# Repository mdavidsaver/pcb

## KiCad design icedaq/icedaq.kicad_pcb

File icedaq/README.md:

iceDAQ
======

Spec.

* 2x DAC
* 2x ADC
* 4x DIO
* SPI interface to controller
* Raspberry Pi Hat
* iCE40 FPGA

Connections to iCE40 FPGA
-------------------------

Programming interface for iCE40 is attached to SPI1 of CPU.  Low speed SPI1 used to configure FPGA, and for debugging of primary interface.  Uses SPI1_CE2 pin to simplify layout.

iCE40 reset and configuration done connected to GPIO pins.

Application program uses SPI0 of CPU to arbitrary I/O pins of iCE40.  Use SPI0_CE0.

i2c eeprom for rpi hat discovery.

Route global clocks 0 and 1 from CPU to iCE40 global inputs

External crystal oscillator connected to iCE40 global input.

Break out UART0 for no particular reason.

Additional SPI connections to 2x ADC and 2x DAC chips.

Break out 4x GPIO pins to header

Analog output
-------------

Use 2x TI DACx311 series SPI DAC.

Operate w/ 3.3V supply.  Could use 5V supply directly as SPI is MOSI only.

output into opamp in non-inverting topology.  Gain=1.5 gives output range of 0-5V from 0-3.3V input.

opamp output has space for series and ground termination.

Analog input
------------

Use 3x TI ADC082S021 (50 KS/S -> 200 KS/S) two channel ADC.  Only one channel per chip used.

Operate w/ 3.3V supply.

input from opamp in non-inverting topology through 0.66 resistor divider (5V -> 3.3V).
opamp gain=1.

input of opamp has space for series and ground termination, also option of AC coupling w/ resistor bias network.

Op Amp
------

Microchip MCP6001 quad rail-to-rail opamp.

Operate w/ 5V supply.

Power budget
------------

Maximum current consumption

3.3V

* iCE40

  <8mA per I/O driver

* eeprom Microchip 24LC23

  <3mA

* 2x DACx311

  short circuit output current @3V = 20mA, @5V = 50mA.

* 2x ADC

  <20mA

* oscillator
* 1.2V regulator

5V

* opamp MCP6001

  <=30 mA
  short circuit output current @1.8V = 6mA, @5.5V = 23 mA

1.2V

* iCE40

  <1mA continuous
  <20mA peak startup

Safety
------

MCP6001 outputs may be shorted w/o damage.  input voltage must be within 1V of supply range.

References
----------

Raspberry Pi

https://github.com/raspberrypi/hats/blob/master/designguide.md

https://pinout.xyz/

https://www.raspberrypi.org/documentation/hardware/raspberrypi/schematics/RPI-3B-V1_2-SCHEMATIC-REDUCED.pdf

iCE40

http://www.latticesemi.com/~/media/LatticeSemi/Documents/Handbooks/iCE40FamilyHandbook.pdf

ADC

http://www.ti.com/lit/ds/symlink/adc082s021.pdf

DAC

http://www.ti.com/lit/ds/symlink/dac5311.pdf

opamp

http://ww1.microchip.com/downloads/en/DeviceDoc/21733j.pdf

eeprom

http://ww1.microchip.com/downloads/en/DeviceDoc/21072G.pdf

iCE40 pins
----------

set_io	GPIO2[0]	1
set_io	GPIO2[1]	2
set_io	GPIO2[2]	3
set_io	GPIO2[3]	4
set_io	GPIO3[0]	18
set_io	GPIO3[1]	19
set_io	GPIO3[2]	20
set_io	GPIO3[3]	21
set_io	GPIO0[3]	27
set_io	GPIO0[2]	28
set_io	GPIO0[1]	29
set_io	GPIO0[0]	30
set_io	GCLK0	33
set_io	GCLK1	34
set_io	SPI1_MISO	45
set_io	SPI1_MOSI	46
set_io	SPI1_SCK	48
set_io	SPI1_CE2	49
set_io	SPI0_CE0	51
set_io	SPI0_SCLK	52
set_io	SPI0_MISO	53
set_io	SPI0_MOSI	54
set_io	ADC0_CE	56
set_io	ADC0_SCK	57
set_io	ADC0_MISO	59
set_io	ADC0_MOSI	60
set_io	ADC1_CE	64
set_io	ADC1_SCK	65
set_io	ADC1_MISO	66
set_io	ADC1_MOSI	68
set_io	DAC0_MOSI	78
set_io	DAC0_SCK	79
set_io	DAC0_SYNC	80
set_io	DAC1_MOSI	82
set_io	DAC1_SCK	83
set_io	DAC1_SYNC	85
set_io	CLK	90

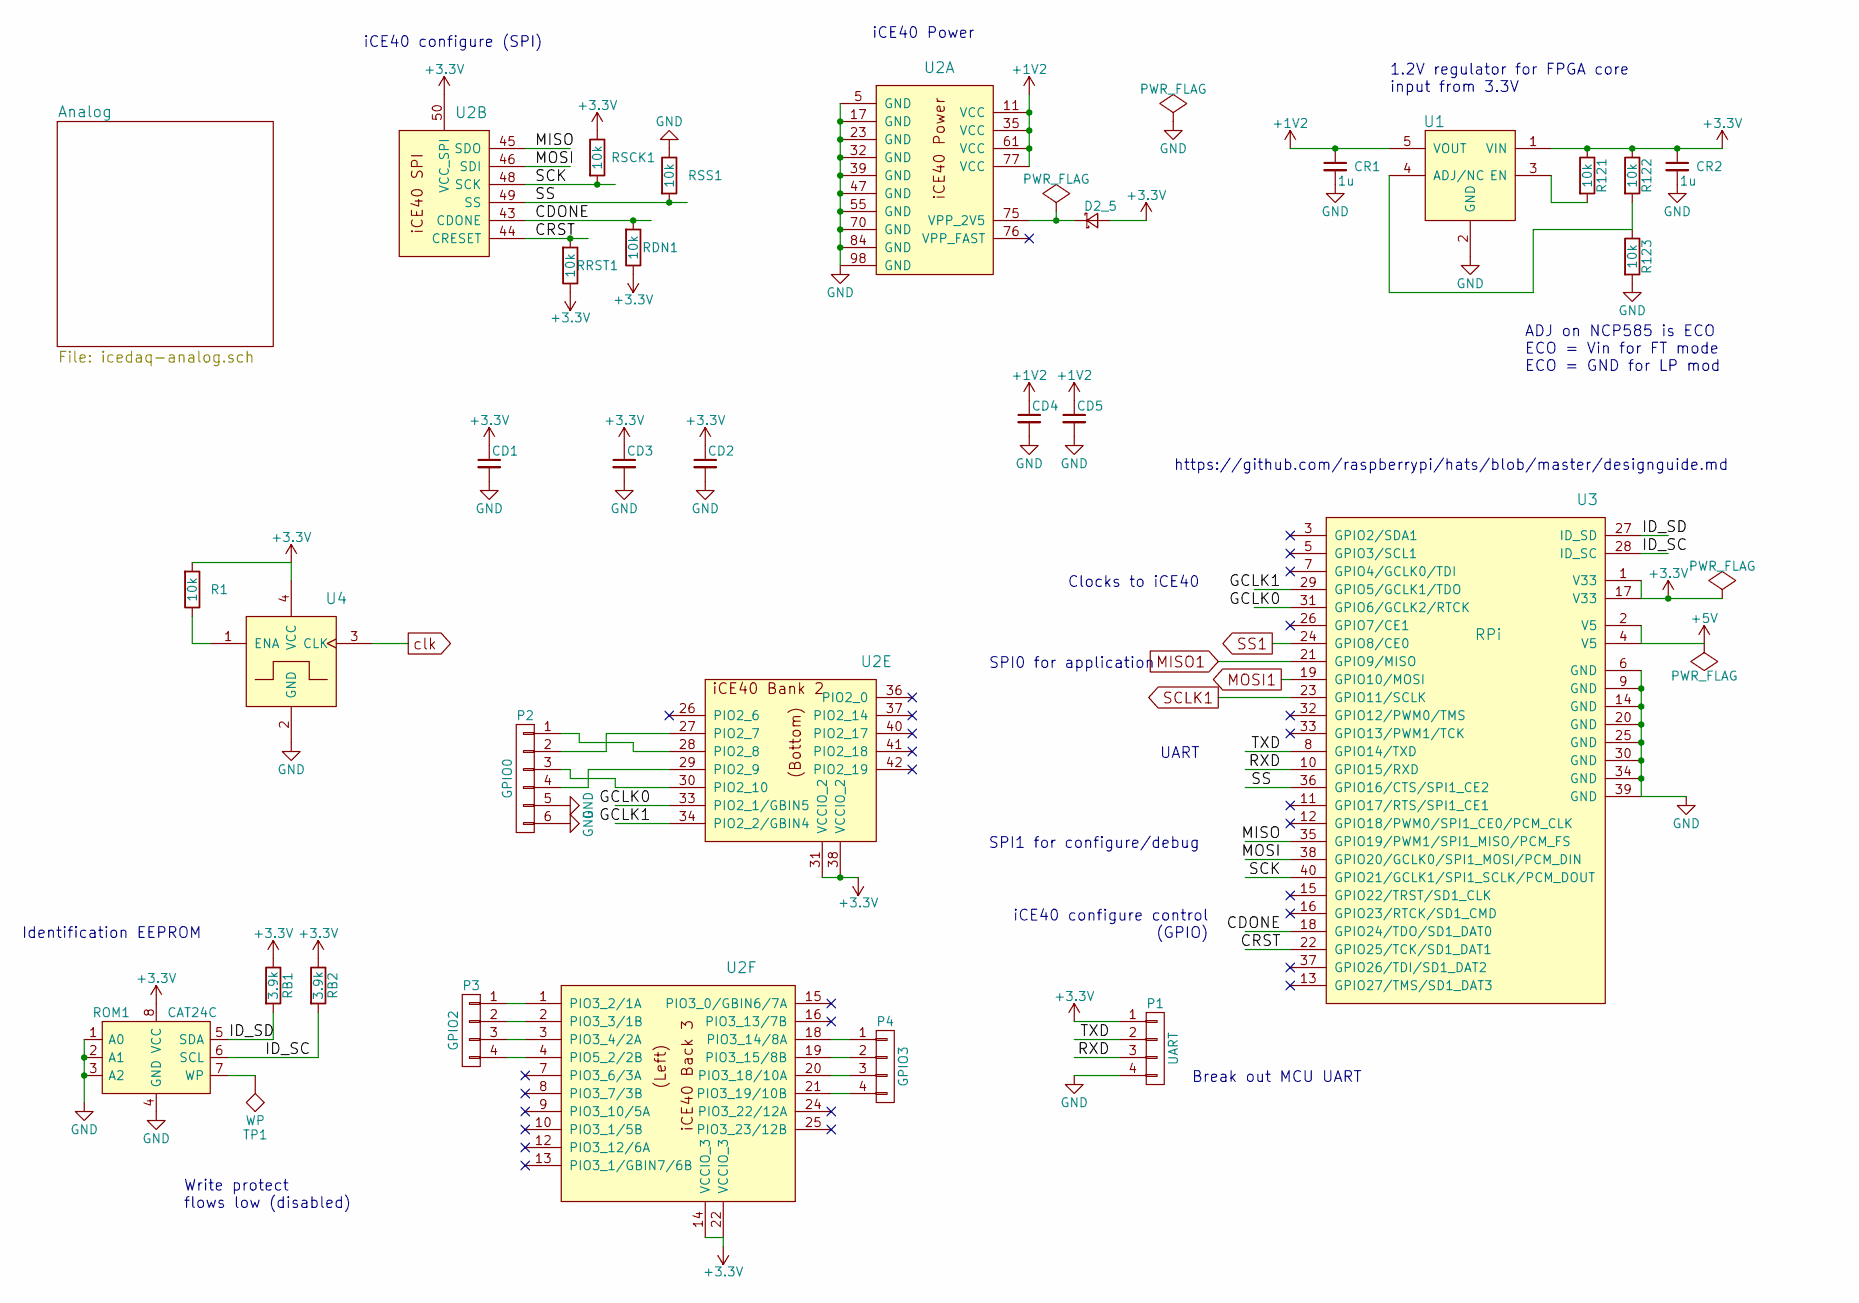
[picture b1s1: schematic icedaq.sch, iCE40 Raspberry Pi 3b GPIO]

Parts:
CD1, CD2, CD3, CD4, CD5: C_Small; C_0603_HandSoldering
CR1, CR2: 1u; C_0603_HandSoldering
D2_5: D_Schottky_Small; D_0603_HandSoldering
P1: UART; Pin_Header_Straight_1x04
P2: GPIO0; Pin_Header_Straight_2x03
P3: GPIO2; gpio
P4: GPIO3; gpio
R1, R121, R122, R123: 10k; R_0603_HandSoldering
RB1, RB2: 3.9k; R_0603_HandSoldering
RDN1: 10k; R_0603_HandSoldering
ROM1: CAT24C; SOIC-8_3.9x4.9mm_Pitch1.27mm
RRST1: 10k; R_0603_HandSoldering
RSCK1: 10k; R_0603_HandSoldering
RSS1: 10k; R_0603_HandSoldering
TP1: WP; testpoint
U1: REG12; SOT23-5
U2: iCE40HX1K-VQ100; VQFP-100
U3: RPi; Pin_Header_Straight_2x20
U4: oscillator4; OSC_SMD_1

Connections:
+1V2: CD4.1, CD5.1, CR1.1, U1.5 (VOUT), U2.11 (VCC), U2.35 (VCC), U2.61 (VCC), U2.77 (VCC)
+3V3: CD1.1, CD2.1, CD3.1, CR2.1, D2_5.2 (A), P1.1, R1.2, R121.1, R122.1, RB1.1, RB2.1, RDN1.1, ROM1.8 (VCC), RRST1.1, RSCK1.1, U1.1 (VIN), U2.14 (VCCIO_3), U2.22 (VCCIO_3), U2.31 (VCCIO_2), U2.38 (VCCIO_2), U2.50 (VCC_SPI), U3.1 (V33), U3.17 (V33), U4.4 (VCC); also elsewhere on the board
+5V: U3.2 (V5), U3.4 (V5); also elsewhere on the board
/CDONE: RDN1.2, U2.43 (CDONE), U3.18 (GPIO24/TDO/SD1_DAT0)
/CRST: RRST1.2, U2.44 (CRESET), U3.22 (GPIO25/TCK/SD1_DAT1)
/GCLK0: U2.33 (PIO2_1/GBIN5), U3.31 (GPIO6/GCLK2/RTCK)
/GCLK1: U2.34 (PIO2_2/GBIN4), U3.29 (GPIO5/GCLK1/TDO)
/ID_SC: RB2.2, ROM1.6 (SCL), U3.28 (ID_SC)
/ID_SD: RB1.2, ROM1.5 (SDA), U3.27 (ID_SD)
/MISO: U2.45 (SDO), U3.35 (GPIO19/PWM1/SPI1_MISO/PCM_FS)
/MOSI: U2.46 (SDI), U3.38 (GPIO20/GCLK0/SPI1_MOSI/PCM_DIN)
/RXD: P1.3, U3.10 (GPIO15/RXD)
/SCK: RSCK1.2, U2.48 (SCK), U3.40 (GPIO21/GCLK1/SPI1_SCLK/PCM_DOUT)
/SS: RSS1.2, U2.49 (SS), U3.36 (GPIO16/CTS/SPI1_CE2)
/TXD: P1.2, U3.8 (GPIO14/TXD)
GND: CD1.2, CD2.2, CD3.2, CD4.2, CD5.2, CR1.2, CR2.2, P1.4, P2.5, P2.6, R123.2, ROM1.1 (A0), ROM1.2 (A1), ROM1.3 (A2), ROM1.4 (GND), RSS1.1, U1.2 (GND), U2.5 (GND), U2.17 (GND), U2.23 (GND), U2.32 (GND), U2.39 (GND), U2.47 (GND), U2.55 (GND), U2.70 (GND), U2.84 (GND), U2.98 (GND), U3.6 (GND), U3.9 (GND), U3.14 (GND), U3.20 (GND), U3.25 (GND), U3.30 (GND), U3.34 (GND), U3.39 (GND), U4.2 (GND); also elsewhere on the board
MISO1: U3.21 (GPIO9/MISO); also elsewhere on the board
MOSI1: U3.19 (GPIO10/MOSI); also elsewhere on the board
unnamed: D2_5.1 (K), U2.75 (VPP_2V5)
unnamed: P2.1, U2.28 (PIO2_8)
unnamed: P2.2, U2.27 (PIO2_7)
unnamed: P2.3, U2.30 (PIO2_10)
unnamed: P2.4, U2.29 (PIO2_9)
unnamed: P3.1, U2.1 (PIO3_2/1A)
unnamed: P3.2, U2.2 (PIO3_3/1B)
unnamed: P3.3, U2.3 (PIO3_4/2A)
unnamed: P3.4, U2.4 (PIO5_2/2B)
unnamed: P4.1, U2.18 (PIO3_14/8A)
unnamed: P4.2, U2.19 (PIO3_15/8B)
unnamed: P4.3, U2.20 (PIO3_18/10A)
unnamed: P4.4, U2.21 (PIO3_19/10B)
unnamed: R1.1, U4.1 (ENA)
unnamed: R121.2, U1.3 (EN)
unnamed: R122.2, R123.1, U1.4 (ADJ/NC)
unnamed: ROM1.7 (WP), TP1.1
SCLK1: U3.23 (GPIO11/SCLK); also elsewhere on the board
SS1: U3.24 (GPIO8/CE0); also elsewhere on the board
clk: U4.3 (CLK); also elsewhere on the board

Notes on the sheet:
1.2V regulator for FPGA core input from 3.3V
ADJ on NCP585 is ECO ECO = Vin for FT mode ECO = GND for LP mod
SPI0 for application
SPI1 for configure/debug
iCE40 configure control (GPIO)
UART
Clocks to iCE40
iCE40 Power
iCE40 configure (SPI)
https://github.com/raspberrypi/hats/blob/master/designguide.md
Break out MCU UART
Write protect flows low (disabled)
Identification EEPROM

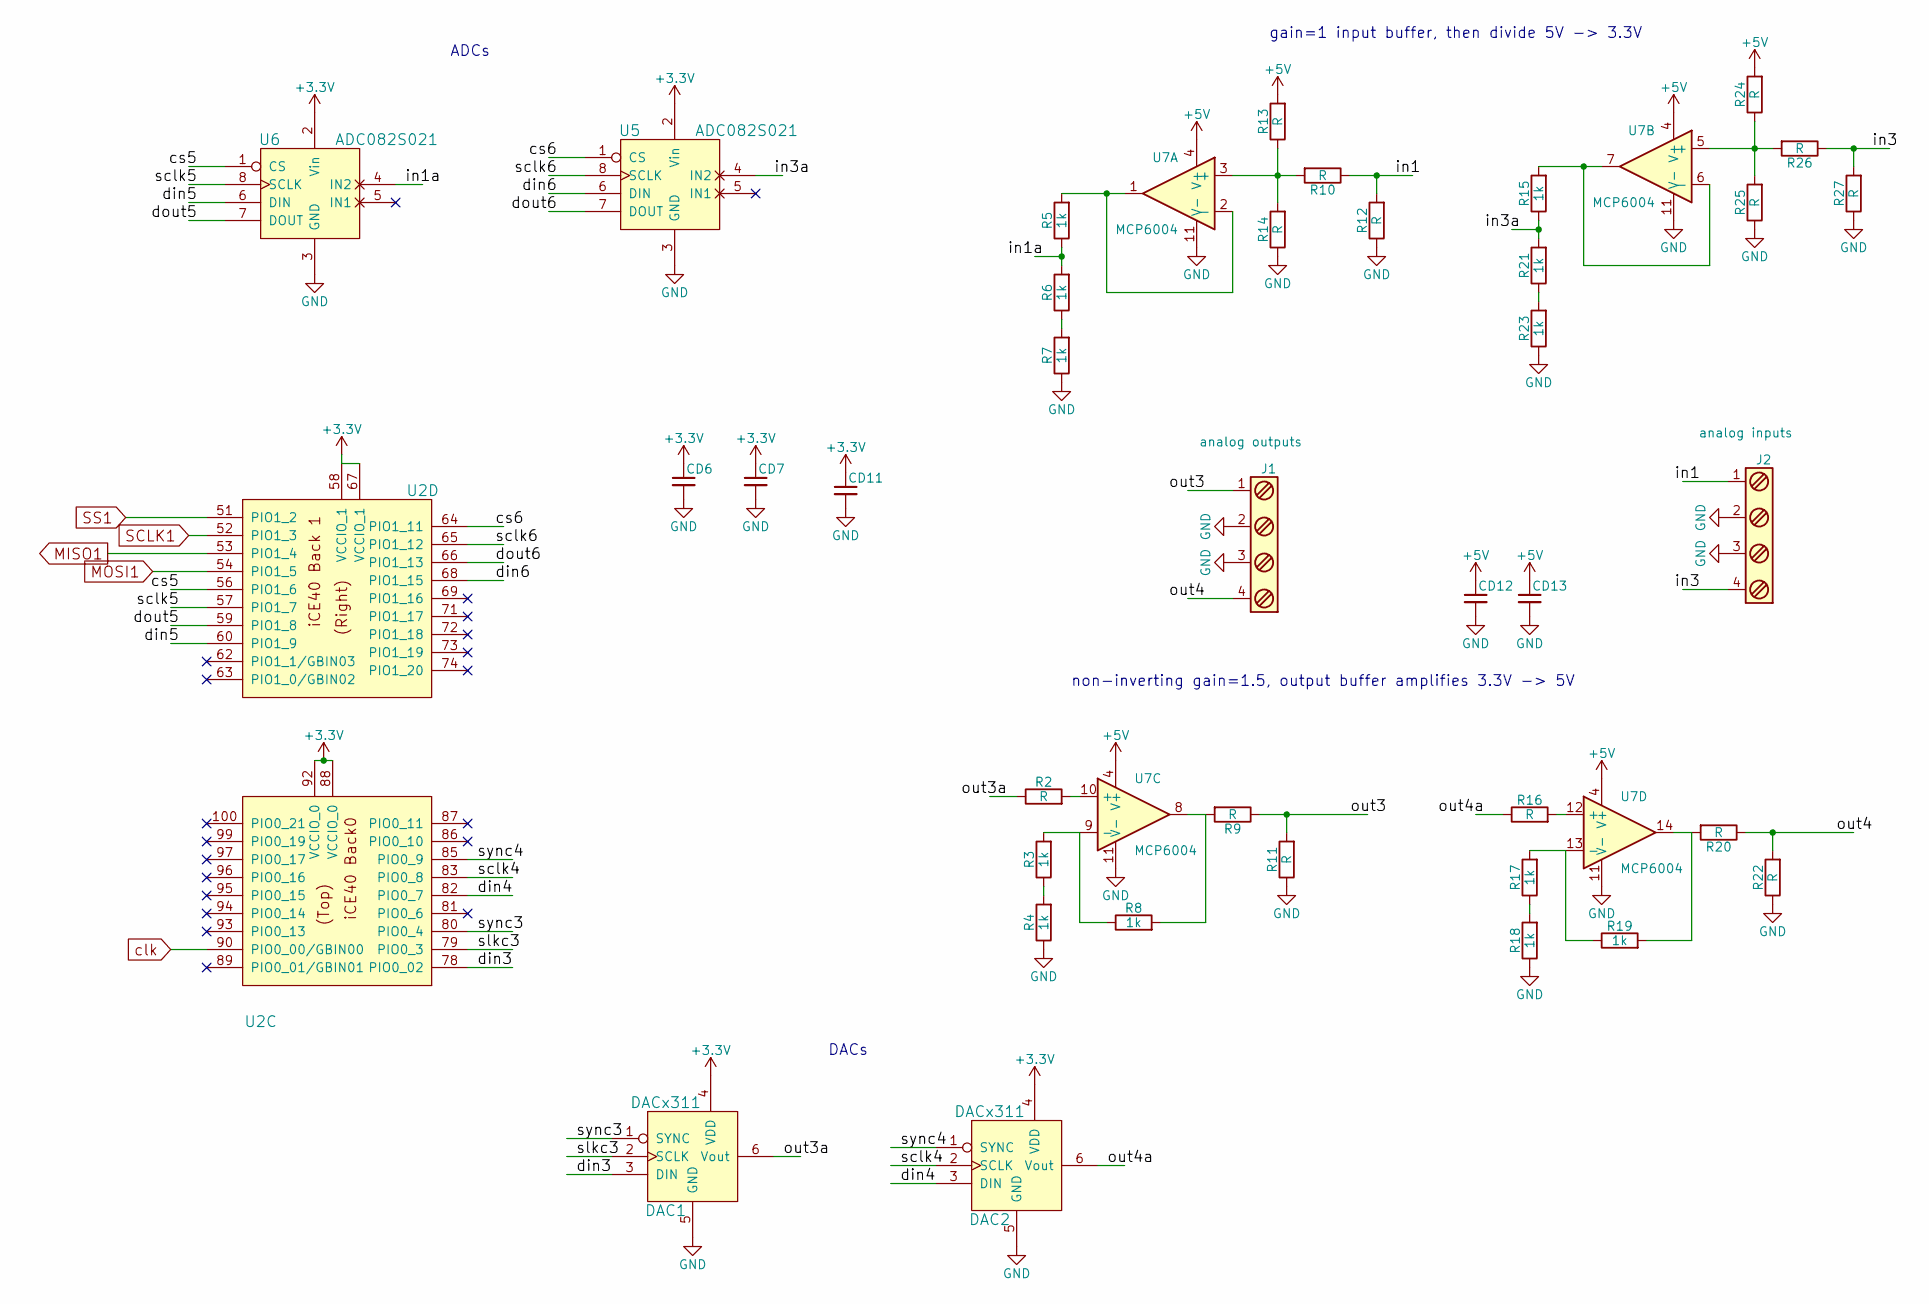
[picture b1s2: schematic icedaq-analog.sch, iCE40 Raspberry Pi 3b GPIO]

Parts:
CD6, CD7, CD11, CD12, CD13: C_Small; C_0603_HandSoldering
DAC1, DAC2: DACx311; SC70
J1: analog outputs; TerminalBlock_Pheonix_MPT-2.54mm_4pol
J2: analog inputs; TerminalBlock_Pheonix_MPT-2.54mm_4pol
R2, R9, R10, R11, R12, R13, R14, R16, R20, R22, R24, R25, R26, R27: R; R_0603_HandSoldering
R3, R4, R5, R6, R7, R8, R15, R17, R18, R19, R21, R23: 1k; R_0603_HandSoldering
U2: iCE40HX1K-VQ100; VQFP-100
U5, U6: ADC082S021; VSSOP-8
U7: MCP6004; SOIC-14

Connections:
+3V3: CD6.1, CD7.1, CD11.1, DAC1.4 (VDD), DAC2.4 (VDD), U2.58 (VCCIO_1), U2.67 (VCCIO_1), U2.88 (VCCIO_0), U2.92 (VCCIO_0), U5.2 (Vin), U6.2 (Vin); also elsewhere on the board
+5V: CD12.1, CD13.1, R13.2, R24.2, U7.4 (V+); also elsewhere on the board
/Analog/cs5: U2.56 (PIO1_6), U6.1 (CS)
/Analog/cs6: U2.64 (PIO1_11), U5.1 (CS)
/Analog/din3: DAC1.3 (DIN), U2.78 (PIO0_02)
/Analog/din4: DAC2.3 (DIN), U2.82 (PIO0_7)
/Analog/din5: U2.60 (PIO1_9), U6.6 (DIN)
/Analog/din6: U2.68 (PIO1_15), U5.6 (DIN)
/Analog/dout5: U2.59 (PIO1_8), U6.7 (DOUT)
/Analog/dout6: U2.66 (PIO1_13), U5.7 (DOUT)
/Analog/in1: J2.1, R10.1, R12.2
/Analog/in1a: R5.1, R6.2, U6.4 (IN2)
/Analog/in3: J2.4, R26.1, R27.2
/Analog/in3a: R15.1, R21.2, U5.4 (IN2)
/Analog/out3: J1.1, R9.1, R11.2
/Analog/out3a: DAC1.6 (Vout), R2.1
/Analog/out4: J1.4, R20.1, R22.2
/Analog/out4a: DAC2.6 (Vout), R16.1
/Analog/sclk4: DAC2.2 (SCLK), U2.83 (PIO0_8)
/Analog/sclk5: U2.57 (PIO1_7), U6.8 (SCLK)
/Analog/sclk6: U2.65 (PIO1_12), U5.8 (SCLK)
/Analog/slkc3: DAC1.2 (SCLK), U2.79 (PIO0_3)
/Analog/sync3: DAC1.1 (SYNC), U2.80 (PIO0_4)
/Analog/sync4: DAC2.1 (SYNC), U2.85 (PIO0_9)
GND: CD6.2, CD7.2, CD11.2, CD12.2, CD13.2, DAC1.5 (GND), DAC2.5 (GND), J1.2, J1.3, J2.2, J2.3, R4.1, R7.1, R11.1, R12.1, R14.1, R18.1, R22.1, R23.1, R25.1, R27.1, U5.3 (GND), U6.3 (GND), U7.11 (V-); also elsewhere on the board
MISO1: U2.53 (PIO1_4); also elsewhere on the board
MOSI1: U2.54 (PIO1_5); also elsewhere on the board
unnamed: R2.2, U7.10 (+)
unnamed: R3.1, R4.2
unnamed: R3.2, R8.1, U7.9 (-)
unnamed: R5.2, U7.1, U7.2 (-)
unnamed: R6.1, R7.2
unnamed: R8.2, R9.2, U7.8
unnamed: R10.2, R13.1, R14.2, U7.3 (+)
unnamed: R15.2, U7.6 (-), U7.7
unnamed: R16.2, U7.12 (+)
unnamed: R17.1, R18.2
unnamed: R17.2, R19.1, U7.13 (-)
unnamed: R19.2, R20.2, U7.14
unnamed: R21.1, R23.2
unnamed: R24.1, R25.2, R26.2, U7.5 (+)
SCLK1: U2.52 (PIO1_3); also elsewhere on the board
SS1: U2.51 (PIO1_2); also elsewhere on the board
clk: U2.90 (PIO0_00/GBIN00); also elsewhere on the board

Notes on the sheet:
gain=1 input buffer, then divide 5V -> 3.3V
non-inverting gain=1.5, output buffer amplifies 3.3V -> 5V
ADCs
DACs

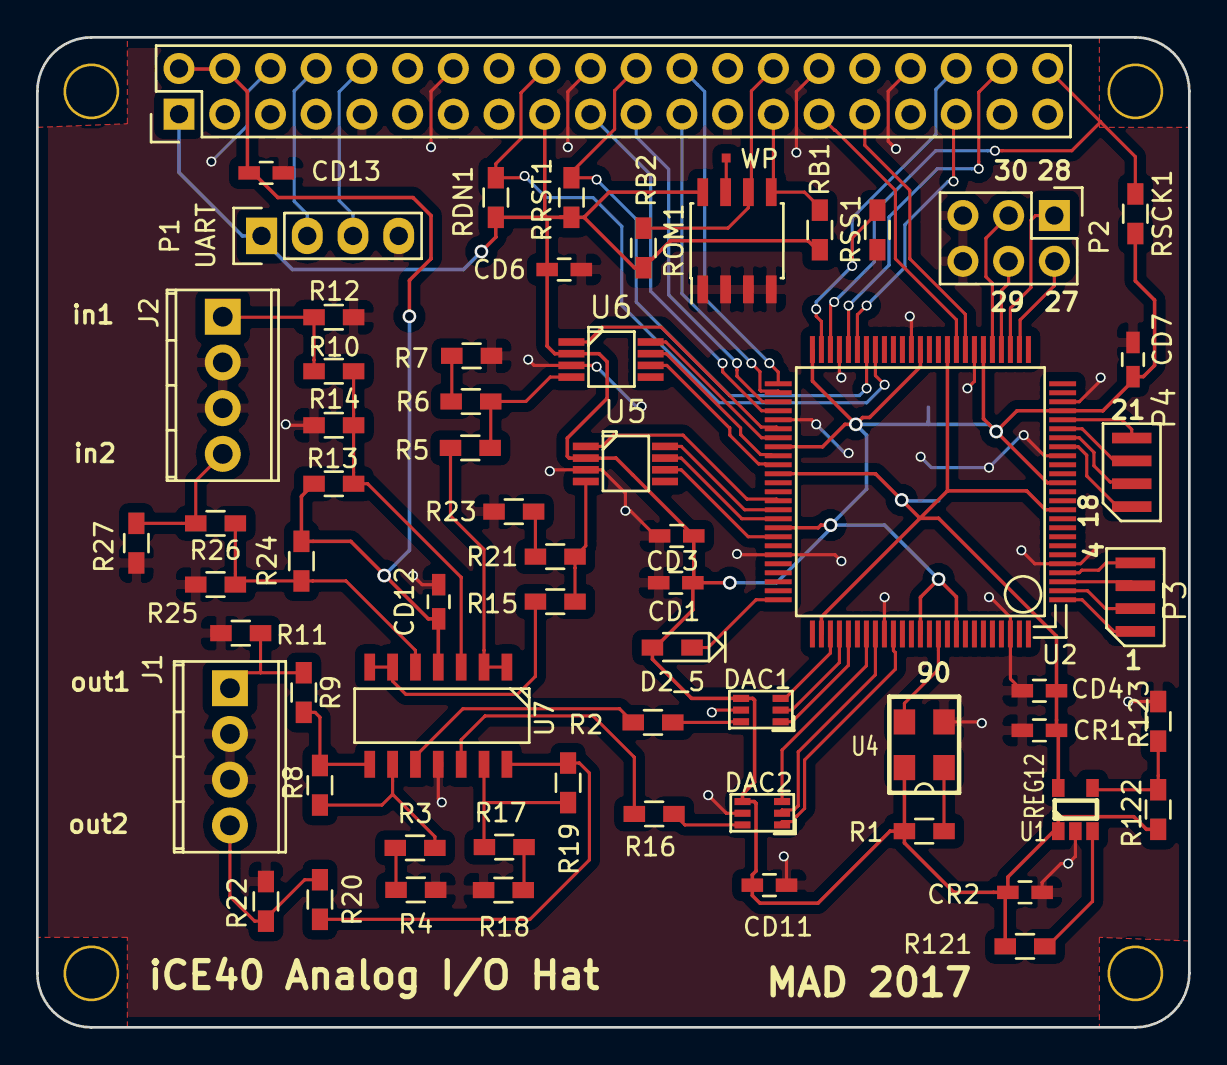
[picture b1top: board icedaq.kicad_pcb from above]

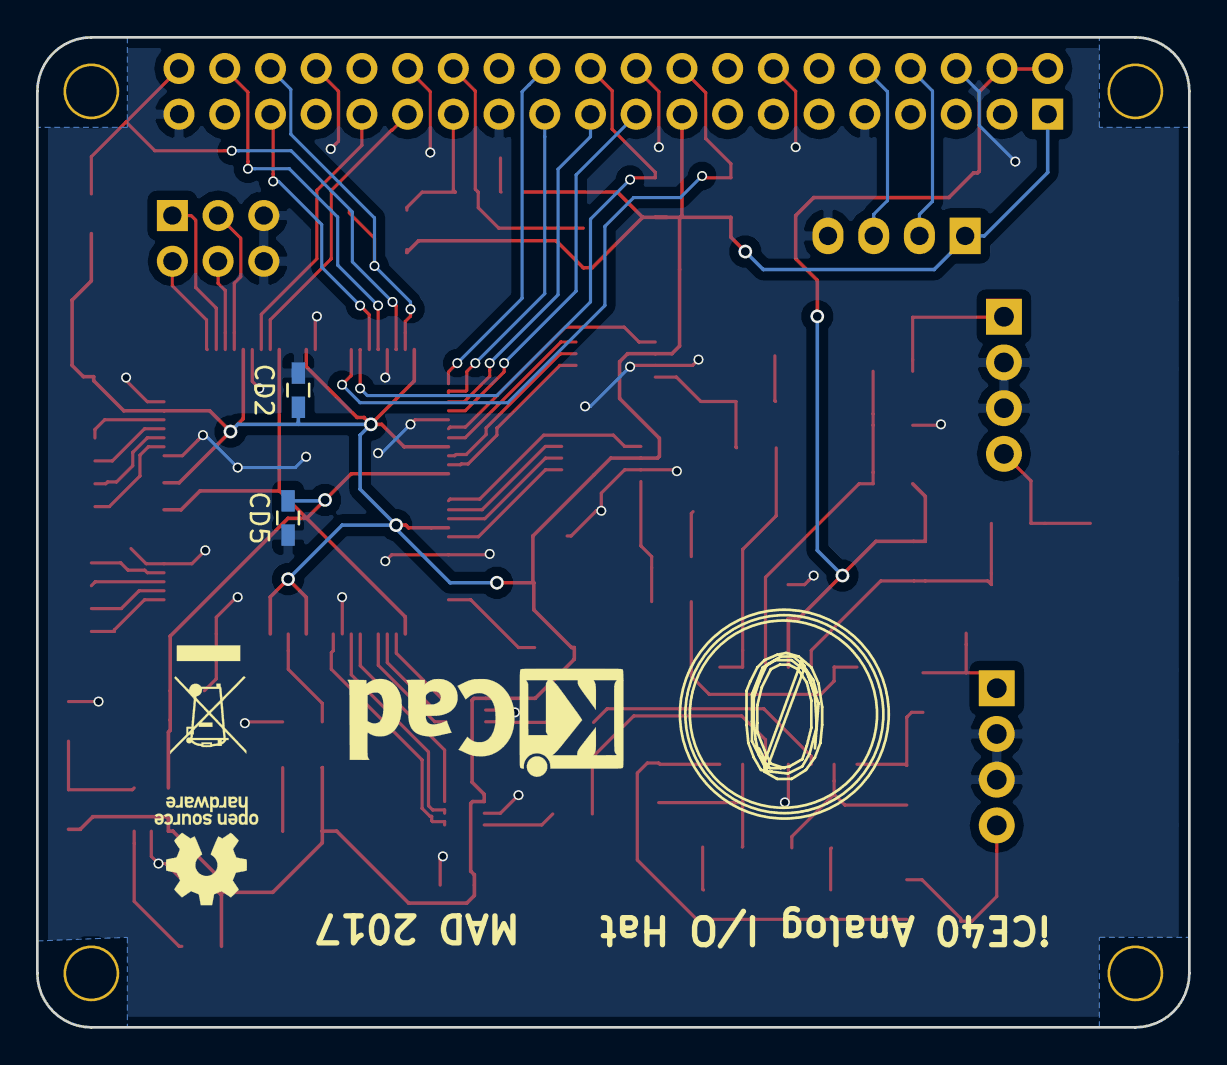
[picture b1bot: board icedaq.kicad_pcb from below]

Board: 2 copper layers, 64.0 x 55.0 mm, 67 parts (2 on the bottom side), 74 nets.

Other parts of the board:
MNT1: MountingHole_3mm

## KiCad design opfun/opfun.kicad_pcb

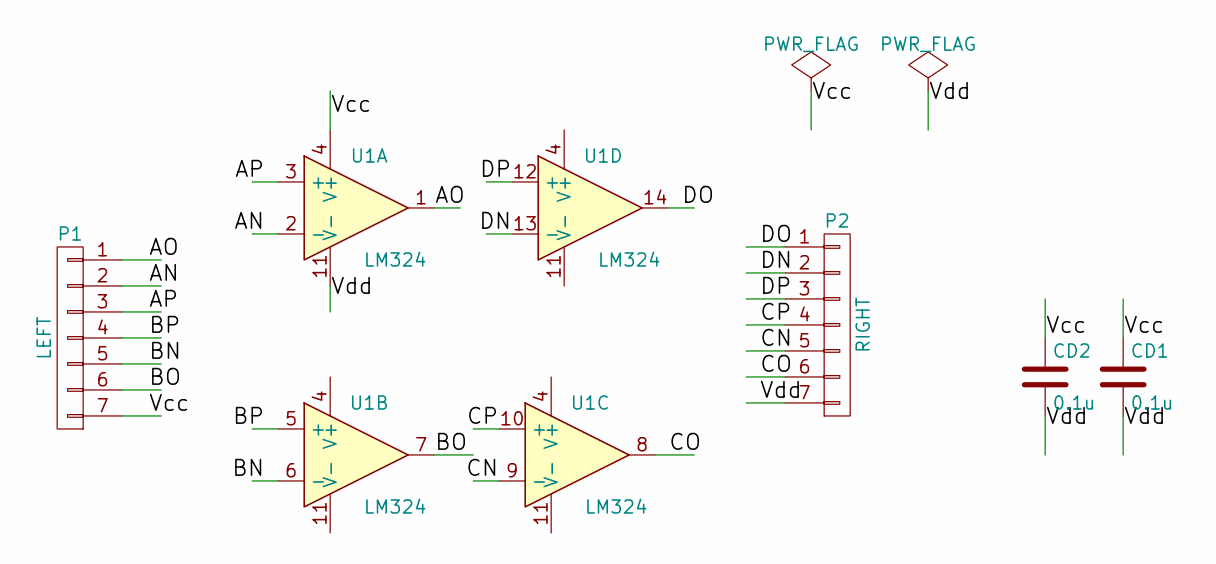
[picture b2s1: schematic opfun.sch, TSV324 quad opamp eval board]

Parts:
CD1, CD2: 0.1u; C_0603_HandSoldering
P1: LEFT; Pin_Header_Straight_1x07
P2: RIGHT; Pin_Header_Straight_1x07
U1: LM324; TSSOP-14

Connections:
/AN: P1.2, U1.2 (-)
/AO: P1.1, U1.1
/AP: P1.3, U1.3 (+)
/BN: P1.5, U1.6 (-)
/BO: P1.6, U1.7
/BP: P1.4, U1.5 (+)
/CN: P2.5, U1.9 (-)
/CO: P2.6, U1.8
/CP: P2.4, U1.10 (+)
/DN: P2.2, U1.13 (-)
/DO: P2.1, U1.14
/DP: P2.3, U1.12 (+)
/Vcc: CD1.1, CD2.1, P1.7, U1.4 (V+)
/Vdd: CD1.2, CD2.2, P2.7, U1.11 (V-)

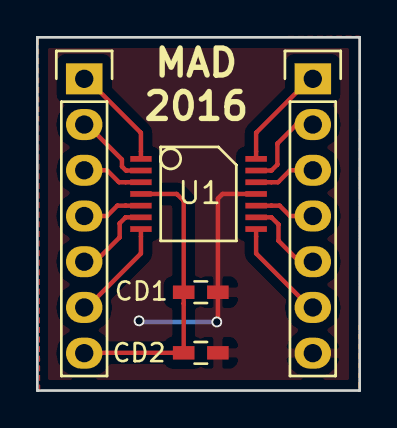
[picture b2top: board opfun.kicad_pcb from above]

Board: 2 copper layers, 17.9 x 19.6 mm, 5 parts (0 on the bottom side), 14 nets.

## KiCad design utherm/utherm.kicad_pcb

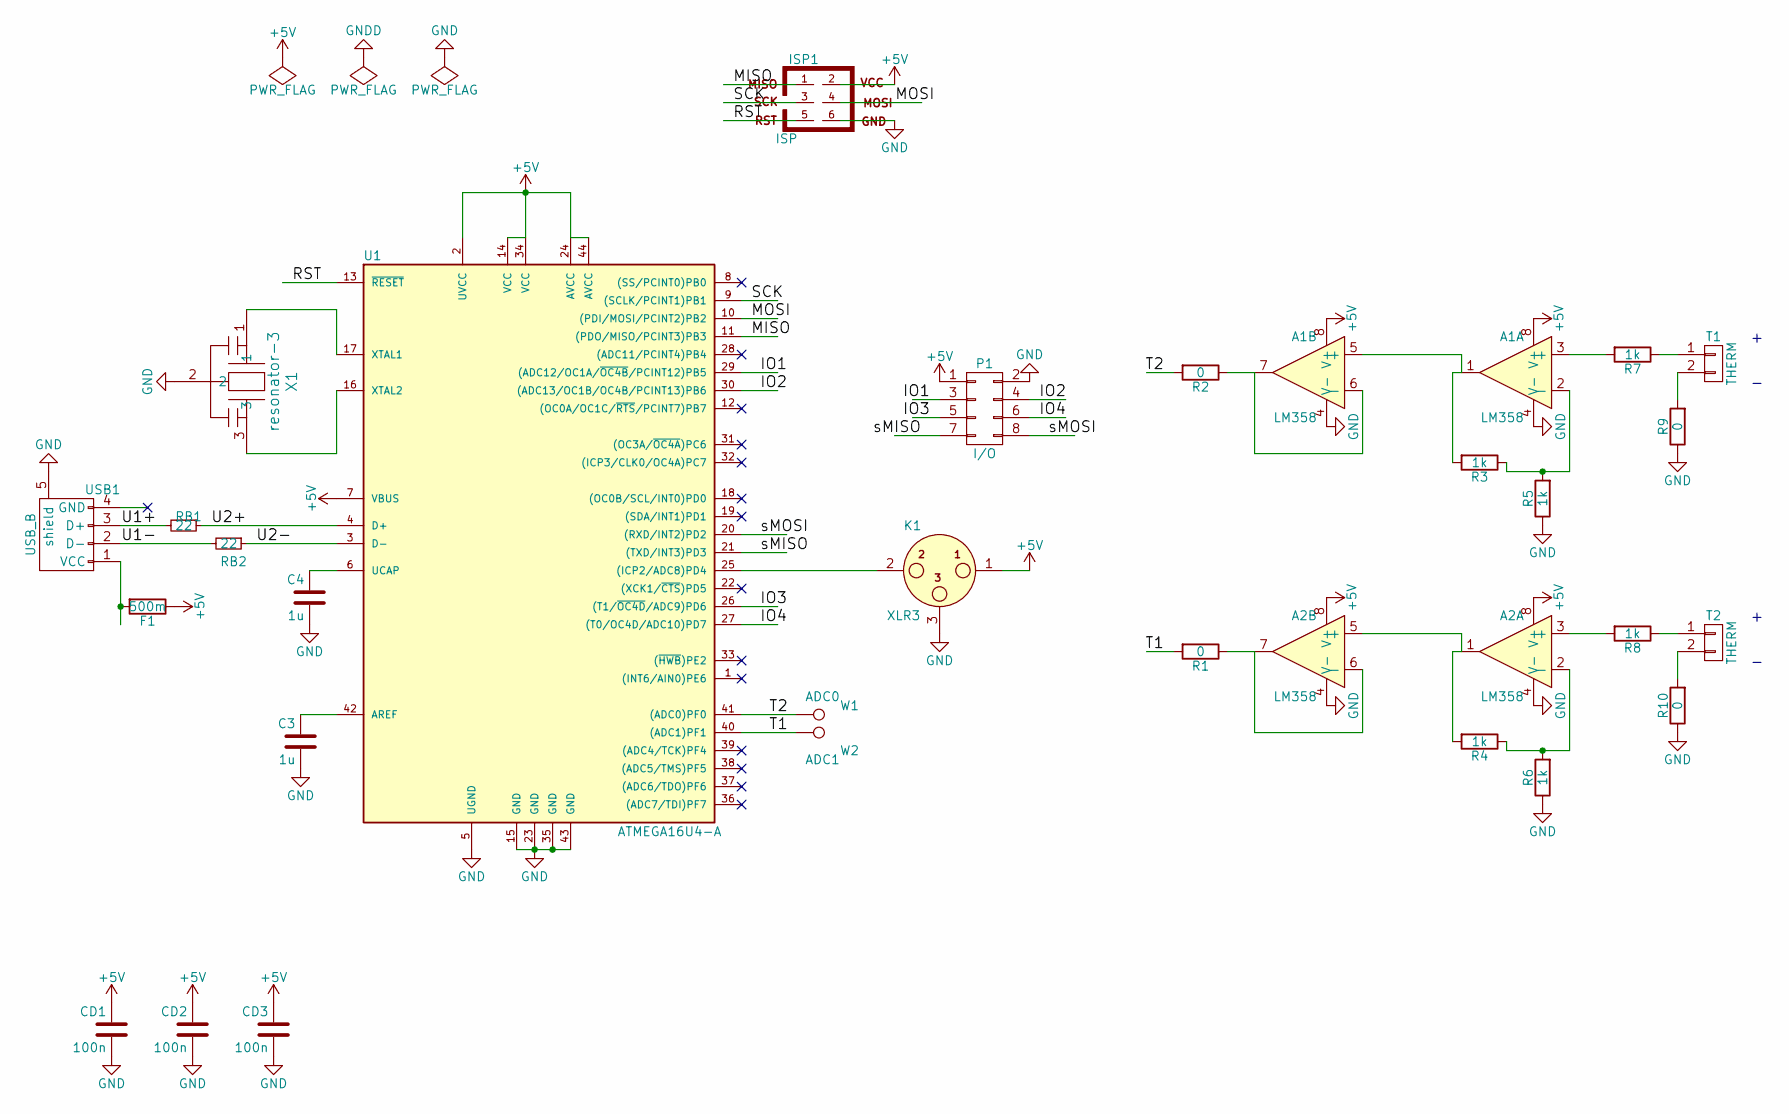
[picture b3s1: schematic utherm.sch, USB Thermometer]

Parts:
A1, A2: LM358; SO8_6mm
C3, C4: 1u; C_0603_HandSoldering
CD1, CD2, CD3: 100n; C_0603_HandSoldering
F1: 500m; R_1218_HandSoldering
ISP1: ISP; Pin_Header_Straight_2x03
K1: XLR3; TO-92_Molded_Narrow
P1: I/O; Pin_Header_Straight_2x04
R1, R2, R9, R10: 0; R_0603_HandSoldering
R3, R4, R5, R6, R7, R8: 1k; R_0603_HandSoldering
RB1, RB2: 22; R_0603_HandSoldering
T1, T2: THERM; TerminalBlock_Pheonix_MKDS1.5-2pol
U1: ATMEGA16U4-A; TQFP44
USB1: USB_B; USB_B_micro
W1: ADC0; Measurement_Point_Square-SMD-Pad_Small
W2: ADC1; Measurement_Point_Square-SMD-Pad_Small
X1: resonator-3

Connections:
+5V: A1.8 (V+), A2.8 (V+), CD1.1, CD2.1, CD3.1, F1.1, ISP1.2, K1.1, P1.1, U1.2 (UVCC), U1.7 (VBUS), U1.14 (VCC), U1.24 (AVCC), U1.34 (VCC), U1.44 (AVCC)
/IO1: P1.3, U1.29 ((ADC12/OC1A/~OC4B~/PCINT12)PB5)
/IO2: P1.4, U1.30 ((ADC13/OC1B/OC4B/PCINT13)PB6)
/IO3: P1.5, U1.26 ((T1/~OC4D~/ADC9)PD6)
/IO4: P1.6, U1.27 ((T0/OC4D/ADC10)PD7)
/MISO: ISP1.1, U1.11 ((PDO/MISO/PCINT3)PB3)
/MOSI: ISP1.4, U1.10 ((PDI/MOSI/PCINT2)PB2)
/RST: ISP1.5, U1.13 (~RESET~)
/SCK: ISP1.3, U1.9 ((SCLK/PCINT1)PB1)
/T1: R1.2, U1.40 ((ADC1)PF1), W2.1
/T2: R2.2, U1.41 ((ADC0)PF0), W1.1
/U1+: RB1.2, USB1.3 (D+)
/U1-: RB2.2, USB1.2 (D-)
/U2+: RB1.1, U1.4 (D+)
/U2-: RB2.1, U1.3 (D-)
/sMISO: P1.7, U1.21 ((TXD/INT3)PD3)
/sMOSI: P1.8, U1.20 ((RXD/INT2)PD2)
GND: A1.4 (V-), A2.4 (V-), C3.2, C4.2, CD1.2, CD2.2, CD3.2, ISP1.6, K1.3, P1.2, R5.1, R6.1, R9.1, R10.1, U1.5 (UGND), U1.15 (GND), U1.23 (GND), U1.35 (GND), U1.43 (GND), USB1.5 (shield), X1.2
unnamed: A1.1, A1.5 (+), R3.2
unnamed: A1.2 (-), R3.1, R5.2
unnamed: A1.3 (+), R7.2
unnamed: A1.6 (-), A1.7, R2.1
unnamed: A2.1, A2.5 (+), R4.2
unnamed: A2.2 (-), R4.1, R6.2
unnamed: A2.3 (+), R8.2
unnamed: A2.6 (-), A2.7, R1.1
unnamed: C3.1, U1.42 (AREF)
unnamed: C4.1, U1.6 (UCAP)
unnamed: F1.2, USB1.1 (VCC)
unnamed: K1.2, U1.25 ((ICP2/ADC8)PD4)
unnamed: R7.1, T1.1
unnamed: R8.1, T2.1
unnamed: R9.2, T1.2
unnamed: R10.2, T2.2
unnamed: U1.16 (XTAL2), X1.3
unnamed: U1.17 (XTAL1), X1.1

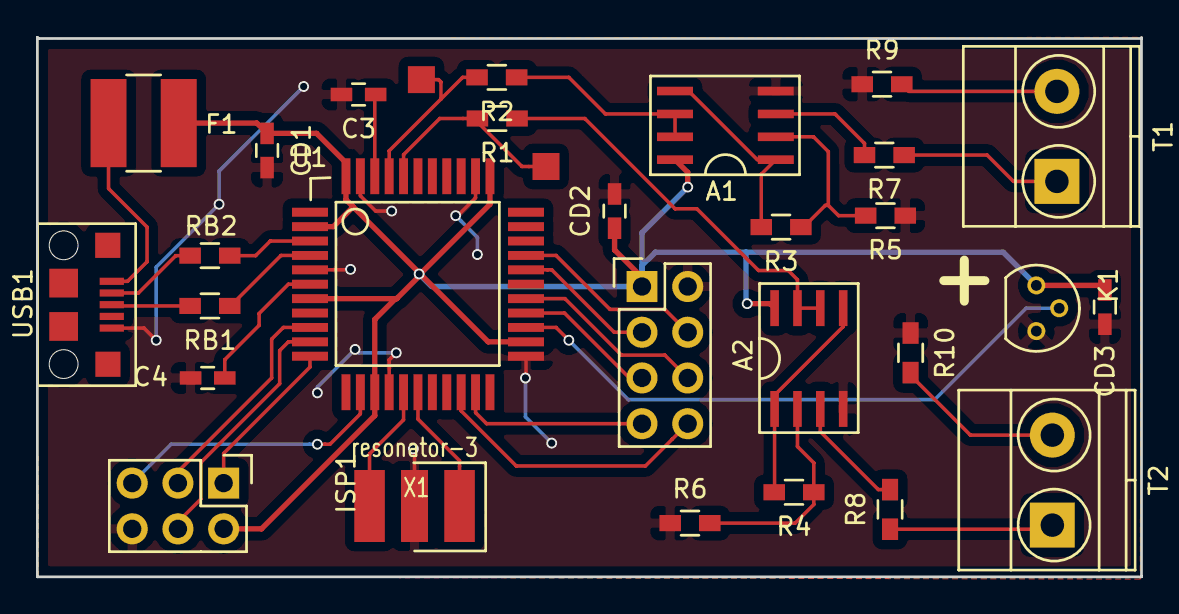
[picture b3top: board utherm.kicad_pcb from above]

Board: 2 copper layers, 61.3 x 30.0 mm, 30 parts (0 on the bottom side), 36 nets.

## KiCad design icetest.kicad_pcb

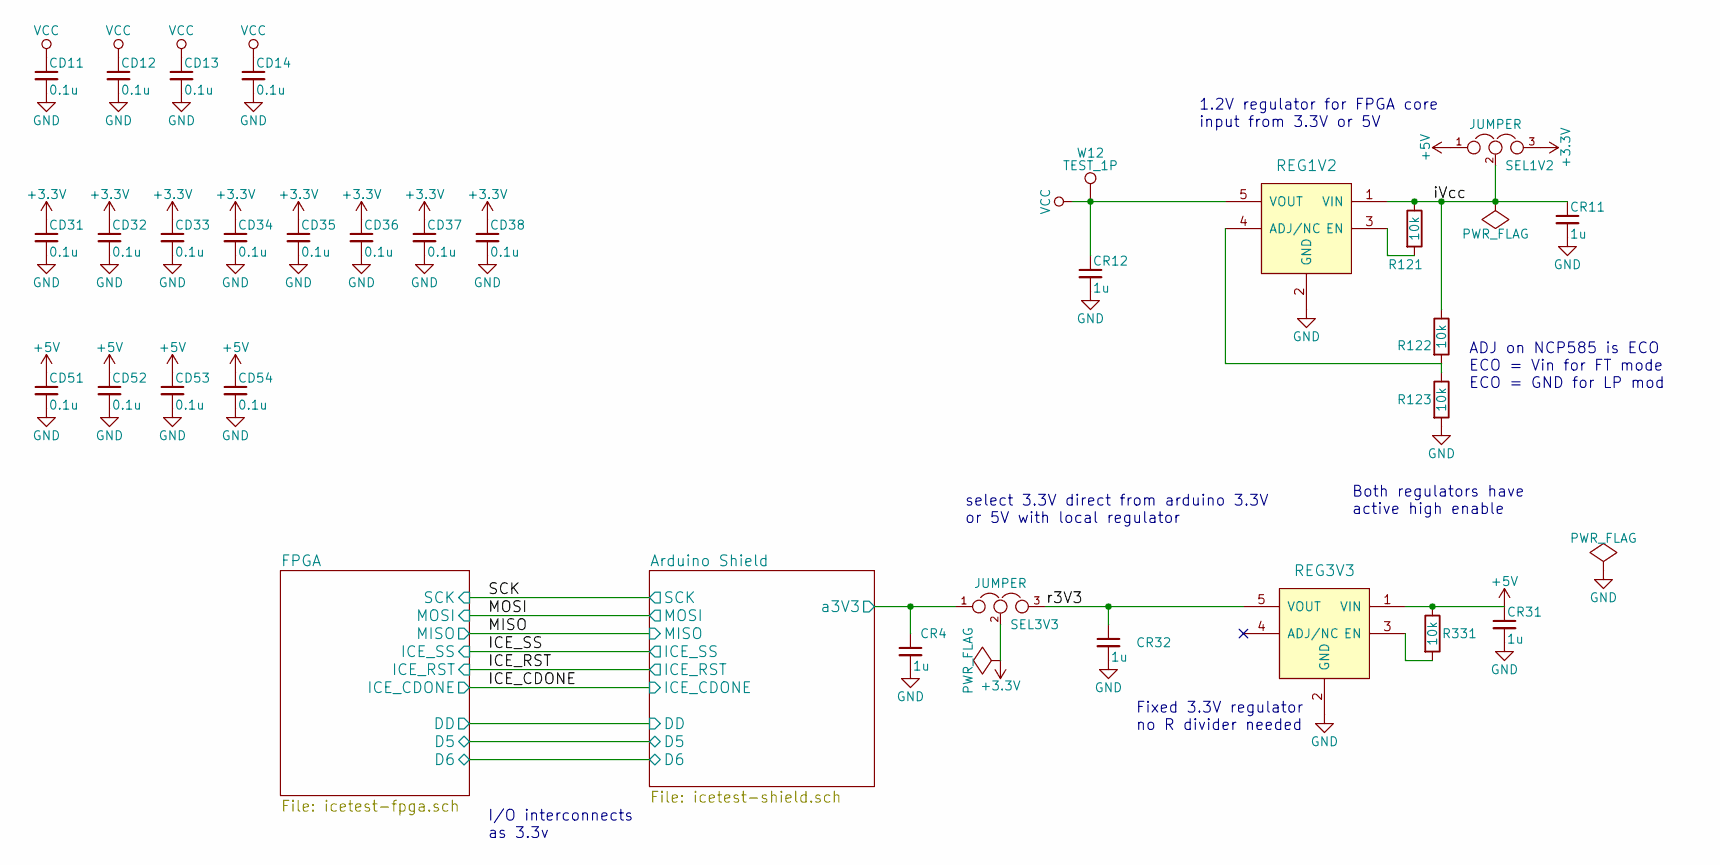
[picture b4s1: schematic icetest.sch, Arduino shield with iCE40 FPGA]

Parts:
CD11, CD12, CD13, CD14, CD31, CD32, CD33, CD34, CD35, CD36, CD37, CD38, CD51, CD52, CD53, CD54: 0.1u; C_0603_HandSoldering
CR4, CR11, CR12, CR31, CR32: 1u; C_0603_HandSoldering
R121, R122, R123, R331: 10k; R_0603_HandSoldering
REG1V2, REG3V3: regulator5; SOT23-5
SEL1V2, SEL3V3: JUMPER; Pin_Header_Straight_1x03
W12: TEST_1P; Measurement_Point_Square-SMD-Pad_Small

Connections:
+3V3: CD31.1, CD32.1, CD33.1, CD34.1, CD35.1, CD36.1, CD37.1, CD38.1, SEL1V2.3, SEL3V3.2; also elsewhere on the board
+5V: CD51.1, CD52.1, CD53.1, CD54.1, CR31.1, R331.1, REG3V3.1 (VIN), SEL1V2.1; also elsewhere on the board
/Arduino Shield/a3V3: CR4.1, SEL3V3.1; also elsewhere on the board
/iVcc: CR11.1, R121.1, R122.1, REG1V2.1 (VIN), SEL1V2.2
/r3V3: CR32.1, REG3V3.5 (VOUT), SEL3V3.3
GND: CD11.2, CD12.2, CD13.2, CD14.2, CD31.2, CD32.2, CD33.2, CD34.2, CD35.2, CD36.2, CD37.2, CD38.2, CD51.2, CD52.2, CD53.2, CD54.2, CR4.2, CR11.2, CR12.2, CR31.2, CR32.2, R123.2, REG1V2.2 (GND), REG3V3.2 (GND); also elsewhere on the board
unnamed: R121.2, REG1V2.3 (EN)
unnamed: R122.2, R123.1, REG1V2.4 (ADJ/NC)
unnamed: R331.2, REG3V3.3 (EN)
VCC: CD11.1, CD12.1, CD13.1, CD14.1, CR12.1, REG1V2.5 (VOUT), W12.1; also elsewhere on the board

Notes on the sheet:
select 3.3V direct from arduino 3.3V or 5V with local regulator
1.2V regulator for FPGA core input from 3.3V or 5V
ADJ on NCP585 is ECO ECO = Vin for FT mode ECO = GND for LP mod
Fixed 3.3V regulator no R divider needed
Both regulators have active high enable
I/O interconnects as 3.3v

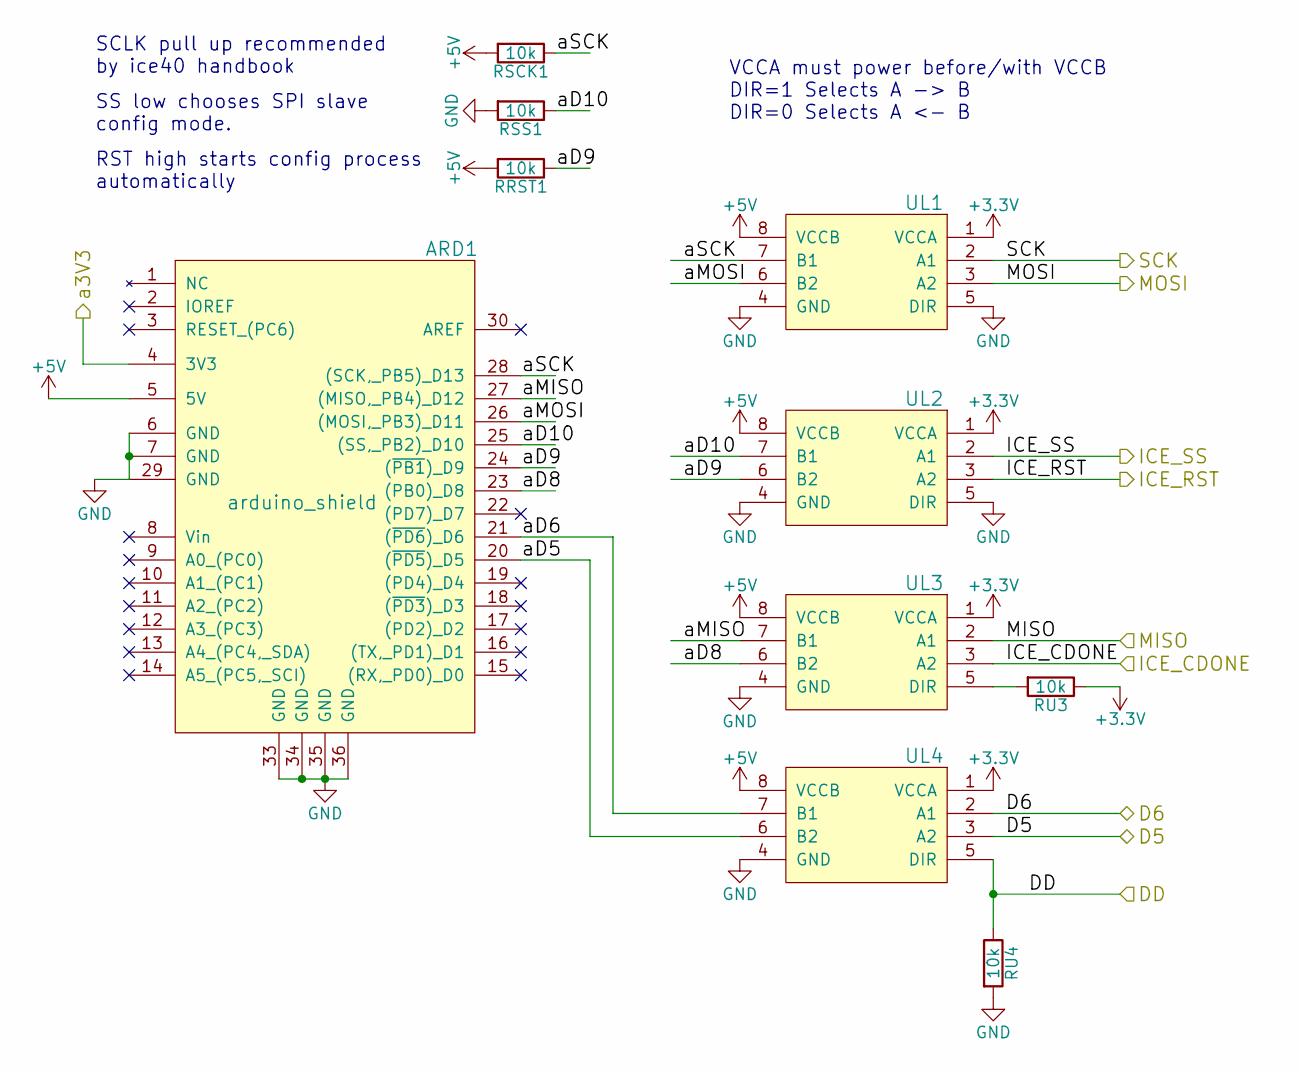
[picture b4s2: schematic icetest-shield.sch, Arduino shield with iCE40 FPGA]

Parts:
ARD1: arduino_shield
RRST1: 10k; R_0603_HandSoldering
RSCK1: 10k; R_0603_HandSoldering
RSS1: 10k; R_0603_HandSoldering
RU3, RU4: 10k; R_0603_HandSoldering
UL1, UL2, UL3, UL4: sn74lvc2t45; VSSOP-8

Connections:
+3V3: RU3.1, UL1.1 (VCCA), UL2.1 (VCCA), UL3.1 (VCCA), UL4.1 (VCCA); also elsewhere on the board
+5V: ARD1.5 (5V), RRST1.2, RSCK1.2, UL1.8 (VCCB), UL2.8 (VCCB), UL3.8 (VCCB), UL4.8 (VCCB); also elsewhere on the board
/Arduino Shield/D5: UL4.3 (A2); also elsewhere on the board
/Arduino Shield/D6: UL4.2 (A1); also elsewhere on the board
/Arduino Shield/DD: RU4.1, UL4.5 (DIR); also elsewhere on the board
/Arduino Shield/ICE_CDONE: UL3.3 (A2); also elsewhere on the board
/Arduino Shield/ICE_RST: UL2.3 (A2); also elsewhere on the board
/Arduino Shield/ICE_SS: UL2.2 (A1); also elsewhere on the board
/Arduino Shield/MISO: UL3.2 (A1); also elsewhere on the board
/Arduino Shield/MOSI: UL1.3 (A2); also elsewhere on the board
/Arduino Shield/SCK: UL1.2 (A1); also elsewhere on the board
/Arduino Shield/a3V3: ARD1.4 (3V3); also elsewhere on the board
/Arduino Shield/aD5: ARD1.20 ((~PD5)_D5), UL4.6 (B2)
/Arduino Shield/aD6: ARD1.21 ((~PD6)_D6), UL4.7 (B1)
/Arduino Shield/aD8: ARD1.23 ((PB0)_D8), UL3.6 (B2)
/Arduino Shield/aD9: ARD1.24 ((~PB1)_D9), RRST1.1, UL2.6 (B2)
/Arduino Shield/aD10: ARD1.25 ((SS,_PB2)_D10), RSS1.1, UL2.7 (B1)
/Arduino Shield/aMISO: ARD1.27 ((MISO,_PB4)_D12), UL3.7 (B1)
/Arduino Shield/aMOSI: ARD1.26 ((MOSI,_PB3)_D11), UL1.6 (B2)
/Arduino Shield/aSCK: ARD1.28 ((SCK,_PB5)_D13), RSCK1.1, UL1.7 (B1)
GND: ARD1.6 (GND), ARD1.7 (GND), ARD1.29 (GND), ARD1.33 (GND), ARD1.34 (GND), ARD1.35 (GND), ARD1.36 (GND), RSS1.2, RU4.2, UL1.4 (GND), UL1.5 (DIR), UL2.4 (GND), UL2.5 (DIR), UL3.4 (GND), UL4.4 (GND); also elsewhere on the board
unnamed: RU3.2, UL3.5 (DIR)

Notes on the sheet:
VCCA must power before/with VCCB DIR=1 Selects A -> B DIR=0 Selects A <- B
SS low chooses SPI slave config mode.
SCLK pull up recommended by ice40 handbook
RST high starts config process automatically
